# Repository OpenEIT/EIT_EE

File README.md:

# Spectra PDF

The schematic for the 32 electrode EIT system is called Spectra.pdf and is contained in the top level directory. Please let me know if you think it should have any modifications. 

# Eagle_EIT

Note: the following design is an older design for an 8 electrode system. I have a newer better system which was designed in Altium which I'll put up here as soon as crowd supply campaign finalized. In the meantime I'd love it if you wanted to join the mailing list! 

https://www.crowdsupply.com/mindseye-biomedical/spectra

## EIT PCB design in Eagle CAD

Electrical Impedance Tomography is a new way to image conductivity changes inside any mostly liquid medium - such as the human body. It's attractive as it doesn't use ionizing radiation like the X-rays used in a CATSCAN, and could be relatively cheap to mass produce. 

This project is an example of a working system from PCB to firmware to reconstruction algorithm. Further work could certainly improve the resolution, but for now we have functionality in all sub sections. 

This is everything required for the basic 8 electrode design to work. Photo of the assembled PCB included. 

The design is based on the ADuCM350 which has a dedicated high precision front end with 16 bit resolution 160 kSPS data speed.The front end also performs a DFT at the rate of 13.8ms per calculation. This leads to a high performance minimal noise set up, excellent for both R&D or educational purposes. 

In the not too distant future kits may be available with a smaller version of the PCB mounted in a box, an electrode harness for mounting to the body, and all cables required to run. 

This combination would be an excellent educational tool for those researching this area, as it allows you to try most of the reconstruction algorithms or come up with your own and quantify any improvements in results. 

It's the same technique as is used in CATSCAN's, except the current running through the body instead of dangerous ionizing radiation of X-Rays. 

Improvements are welcome to this design. To increase resolution you could make a rotational version which is time resolution limited, or simply add more electrodes and re-compute the reconstruction that way. Another intended improvement is to move to tetrapolar differential electrodes set up. If you'd like to collaborate just pull the repository or email contact@mindseyebiomedical.com

We'd love to hear how you are using this! 

## New Board Design 

We have a newer better board design which is uploaded and called Spectra.pdf. Check it out. 

## Future Plans 

Are hatching! Join the technical discussion list to discuss further at openeit.github.io 

## License 

The Creative Commons Attribution-NonCommercial-ShareAlike 4.0 International License seems to fit best with this project. Check out the human readable summary here: 

<br />This work is licensed under a <a rel="license" href="http://creativecommons.org/licenses/by-nc-sa/4.0/">Creative Commons Attribution-NonCommercial-ShareAlike 4.0 International License</a>.

If you'd like to make a derivative of this project in a commercial setting, we'd love a payment so that we can afford to spend time both maintaining this project and making more projects like this one. If this hybrid open source model works, it would enable open source projects to receive some funding, making the global commons stronger to benefit everyone.

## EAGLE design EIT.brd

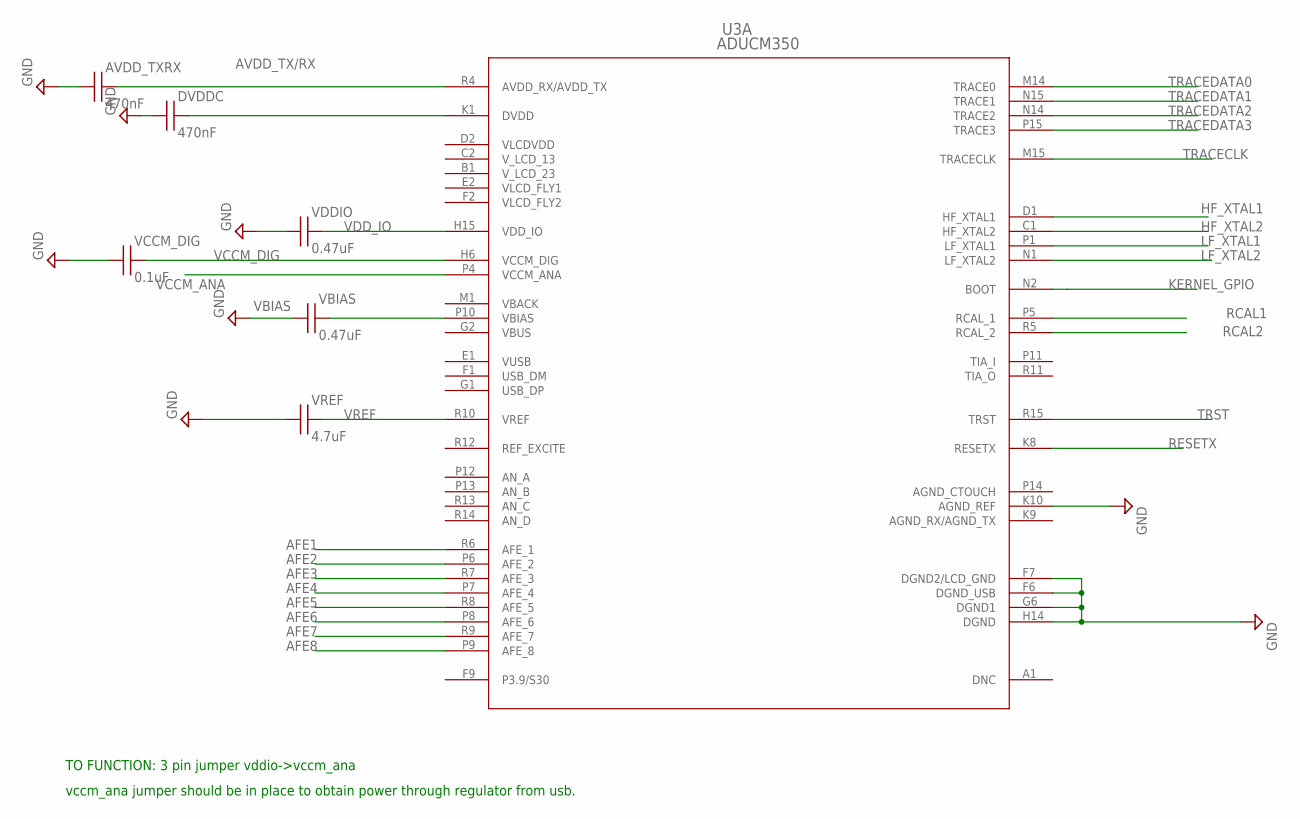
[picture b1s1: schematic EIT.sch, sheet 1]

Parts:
AVDD_TXRX: 470nF; CAPC1608X87N; MPN MCTEA4R7M1HB-0512P
DVDDC: 470nF; CAPC1608X87N; MPN MCTEA4R7M1HB-0512P
U3: ADUCM350; ADUCM350_DUNCAN; MPN ADUCM350BBCZ
VBIAS: 0.47uF; CAPC1608X87N; MPN JMK105BJ474KV-F
VCCM_DIG: 0.1uF; CAPC1608X87N; MPN MC0402X104K100CT
VDDIO: 0.47uF; CAPC1608X87N; MPN JMK105BJ474KV-F
VREF: 4.7uF; CAPC1608X87N; MPN GRM188R60J475ME19D

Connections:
AFE1: U3.R6 (AFE_1); also elsewhere on the board
AFE2: U3.P6 (AFE_2); also elsewhere on the board
AFE3: U3.R7 (AFE_3); also elsewhere on the board
AFE4: U3.P7 (AFE_4); also elsewhere on the board
AFE5: U3.R8 (AFE_5); also elsewhere on the board
AFE6: U3.P8 (AFE_6); also elsewhere on the board
AFE7: U3.R9 (AFE_7); also elsewhere on the board
AFE8: U3.P9 (AFE_8); also elsewhere on the board
AVDD_TX/RX: AVDD_TXRX.2, U3.R4 (AVDD_RX/AVDD_TX)
GND: AVDD_TXRX.1, DVDDC.1, U3.F6 (DGND_USB), U3.F7 (DGND2/LCD_GND), U3.G6 (DGND1), U3.H14 (DGND), U3.K10 (AGND_REF), VBIAS.1, VCCM_DIG.1, VDDIO.1, VREF.1; also elsewhere on the board
HF_XTAL1: U3.D1 (HF_XTAL1); also elsewhere on the board
HF_XTAL2: U3.C1 (HF_XTAL2); also elsewhere on the board
KERNEL_GPIO: U3.N2 (BOOT); also elsewhere on the board
LF_XTAL1: U3.P1 (LF_XTAL1); also elsewhere on the board
LF_XTAL2: U3.N1 (LF_XTAL2); also elsewhere on the board
RCAL1: U3.P5 (RCAL_1); also elsewhere on the board
RCAL2: U3.R5 (RCAL_2); also elsewhere on the board
RESETX: U3.K8 (RESETX); also elsewhere on the board
TRACECLK: U3.M15 (TRACECLK); also elsewhere on the board
TRACEDATA0: U3.M14 (TRACE0); also elsewhere on the board
TRACEDATA1: U3.N15 (TRACE1); also elsewhere on the board
TRACEDATA2: U3.N14 (TRACE2); also elsewhere on the board
TRACEDATA3: U3.P15 (TRACE3); also elsewhere on the board
TRST: U3.R15 (TRST); also elsewhere on the board
VBIAS: U3.P10 (VBIAS), VBIAS.2
VCCM_ANA: U3.P4 (VCCM_ANA); also elsewhere on the board
VCCM_DIG: U3.H6 (VCCM_DIG), VCCM_DIG.2
VDD_IO: U3.H15 (VDD_IO), VDDIO.2; also elsewhere on the board
VLCDVDD: DVDDC.2, U3.K1 (DVDD)
VREF: U3.R10 (VREF), VREF.2

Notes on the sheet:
TO FUNCTION: 3 pin jumper vddio->vccm_ana
vccm_ana jumper should be in place to obtain power through regulator from usb.

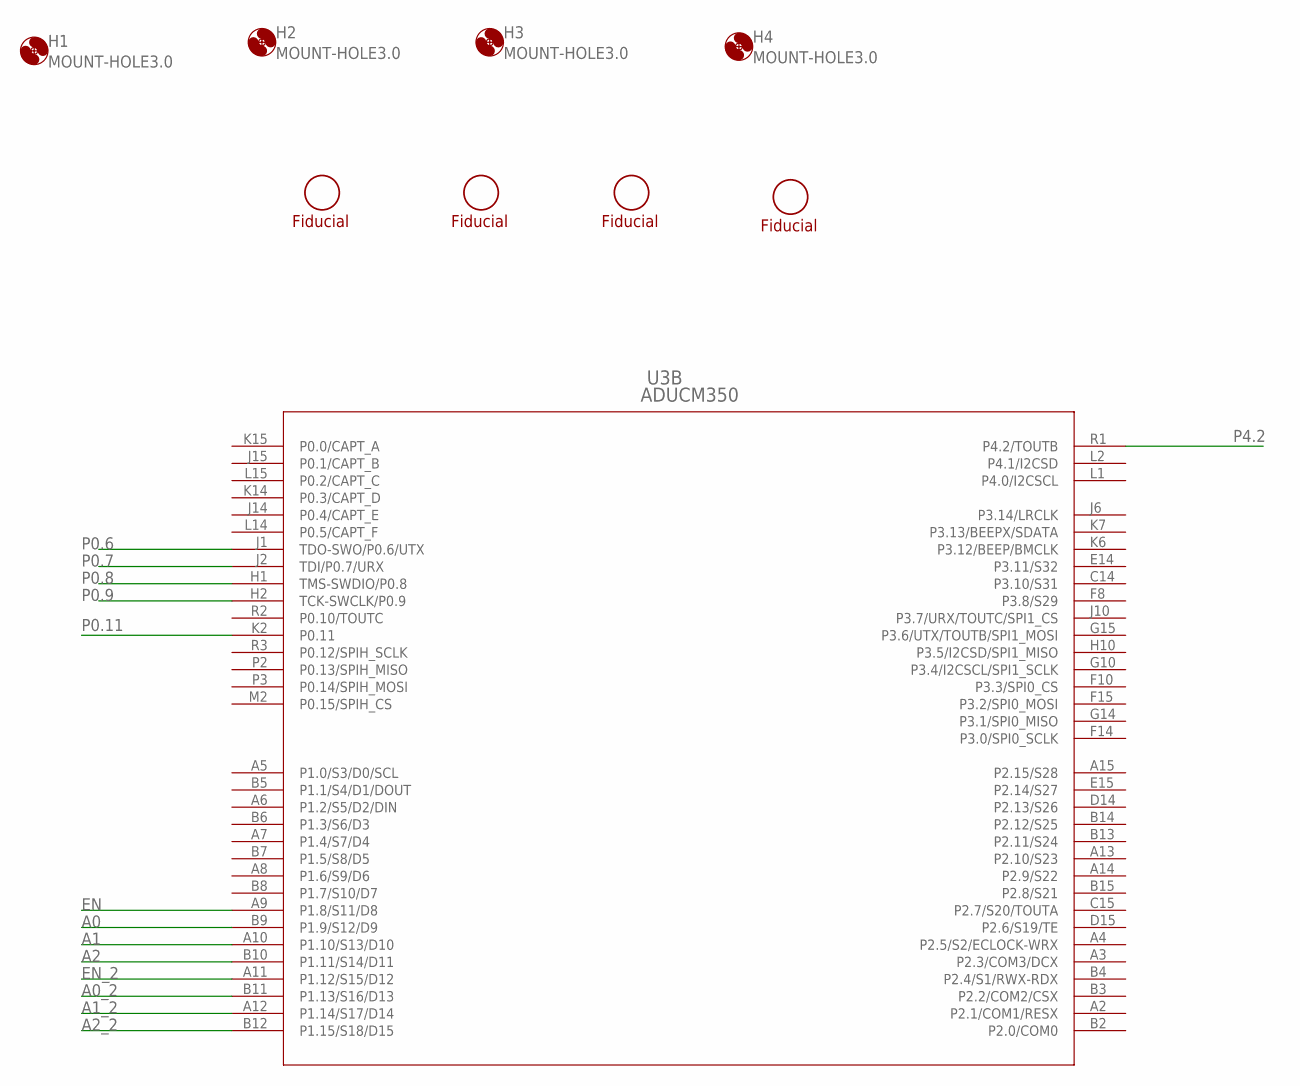
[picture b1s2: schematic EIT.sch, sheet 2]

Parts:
F1, F2, F3, F4: FIDUCIAL; FIDUCIAL-1MM
H1, H2, H3, H4: MOUNT-HOLE3.0; 3,0
U3: ADUCM350; ADUCM350_DUNCAN; MPN ADUCM350BBCZ

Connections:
A0: U3.B9 (P1.9/S12/D9); also elsewhere on the board
A0_2: U3.B11 (P1.13/S16/D13); also elsewhere on the board
A1: U3.A10 (P1.10/S13/D10); also elsewhere on the board
A1_2: U3.A12 (P1.14/S17/D14); also elsewhere on the board
A2: U3.B10 (P1.11/S14/D11); also elsewhere on the board
A2_2: U3.B12 (P1.15/S18/D15); also elsewhere on the board
EN: U3.A9 (P1.8/S11/D8); also elsewhere on the board
EN_2: U3.A11 (P1.12/S15/D12); also elsewhere on the board
P0.6: U3.J1 (TDO-SWO/P0.6/UTX); also elsewhere on the board
P0.7: U3.J2 (TDI/P0.7/URX); also elsewhere on the board
P0.8: U3.H1 (TMS-SWDIO/P0.8); also elsewhere on the board
P0.9: U3.H2 (TCK-SWCLK/P0.9); also elsewhere on the board
P0.11: U3.K2 (P0.11); also elsewhere on the board
P4.2: U3.R1 (P4.2/TOUTB); also elsewhere on the board

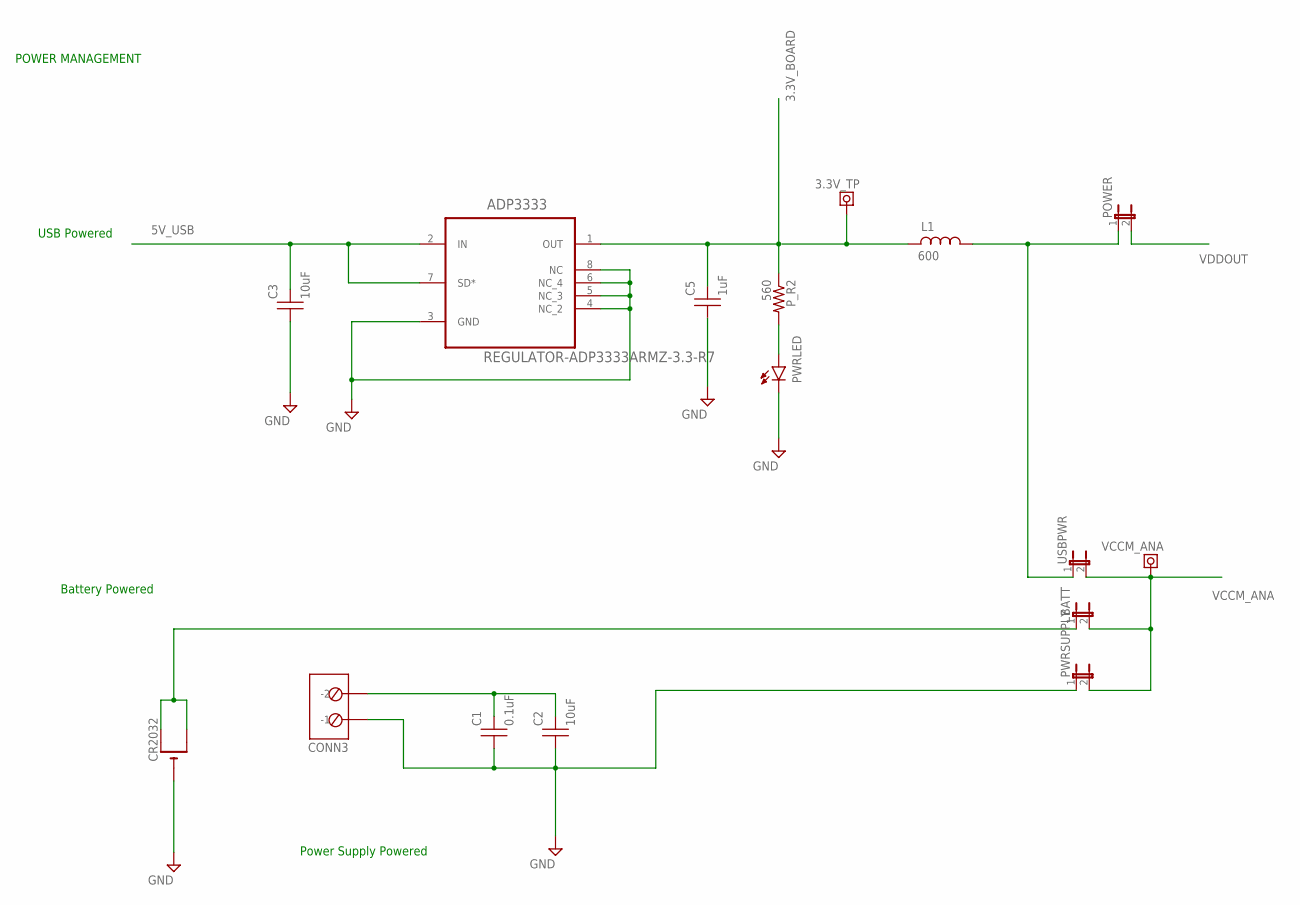
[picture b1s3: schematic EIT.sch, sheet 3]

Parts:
3.3V_TP: TEST_POINT-TEST_POINTMINI; TP-MINI; MPN H2173-05
ADP3333: REGULATOR-ADP3333ARMZ-3.3-R7; SOP65P490X110-8N
BATT: JUMPER-2PTH; 1X02; MPN M20-9990246
C1: 0.1uF; CAPC1608X87N; PARTNO GRM188R71C104KA01D
C2, C3: 10uF; CAPC1608X87N; PARTNO GRM188R60G106ME47D
C5: 1uF; CAPC1608X87N; PARTNO GRM188R60J105KA01D
CONN3: MKDSN2; PARTNO 1729128
CR2032: CR2032SMT; CR2032-SMD; PARTNO 3002TR
L1: 600; CAPC1608X87N; PARTNO BLM18HG601SN1D
POWER: JUMPER-2PTH; 1X02; MPN M20-9990246
PWRLED: LED-0603; 0603_LED; MPN HSML-C191
PWRSUPPLY: JUMPER-2PTH; 1X02; MPN M20-9990246
P_R2: 560; RES1608X55; MPN CRCW0603560RFKEA
USBPWR: JUMPER-2PTH; 1X02; MPN M20-9990246
VCCM_ANA: TEST_POINT-TEST_POINTMINI; TP-MINI; MPN H2173-05

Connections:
3.3V_BOARD: ADP3333.1 (OUT), C5.2, P_R2.2; also elsewhere on the board
5V_USB: ADP3333.2 (IN), ADP3333.7 (SD*), C3.2; also elsewhere on the board
GND: ADP3333.3 (GND), ADP3333.4 (NC_2), ADP3333.5 (NC_3), ADP3333.6 (NC_4), ADP3333.8 (NC), C1.1, C2.1, C3.1, C5.1, CONN3.1 (-1), CR2032.-, PWRLED.C, PWRSUPPLY.1; also elsewhere on the board
unnamed: PWRLED.A, P_R2.1
unnamed: 3.3V_TP.1, L1.1
unnamed: L1.2, POWER.1, USBPWR.1
unnamed: BATT.1, CR2032.+$1 (+), CR2032.+$2 (+1)
unnamed: C1.2, C2.2, CONN3.2 (-2)
VCCM_ANA: BATT.2, PWRSUPPLY.2, USBPWR.2, VCCM_ANA.1; also elsewhere on the board
VDDOUT: POWER.2; also elsewhere on the board

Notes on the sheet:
POWER MANAGEMENT
USB Powered
Battery Powered
Power Supply Powered

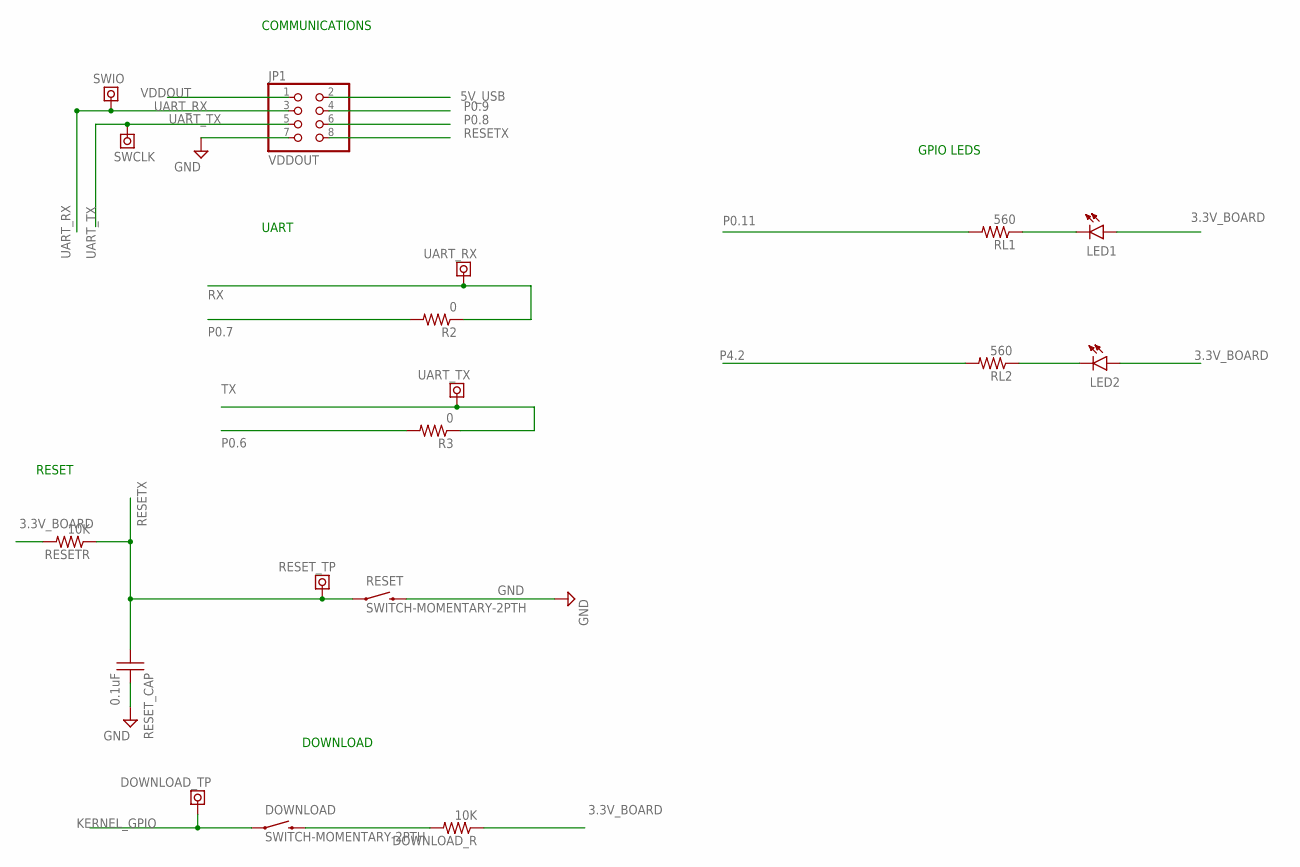
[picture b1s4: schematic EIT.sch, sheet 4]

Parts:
DOWNLOAD: SWITCH-MOMENTARY-2PTH; TACTILE-PTH; MPN B3S-1000
DOWNLOAD_R: 10K; RES1608X55; MPN MC00625W0402110K
DOWNLOAD_TP: TEST_POINT-TEST_POINTMINI; TP-MINI; MPN H2173-05
JP1: VDDOUT; 2X04/90; MPN 27-12209
LED1: LED-0603; 0603_LED; PARTNO 150060YS75000
LED2: LED-0603; 0603_LED; PARTNO 150060GS75000
R2, R3: 0; RES1608X55; PARTNO MCR03EZPJ000
RESET: SWITCH-MOMENTARY-2PTH; TACTILE-PTH; MPN B3S-1000
RESETR: 10K; RES1608X55; PARTNO MCR03EZPFX1002
RESET_CAP: 0.1uF; CAPC1608X87N; MPN C0805C104J5RACTU
RESET_TP: TEST_POINT-TEST_POINTMINI; TP-MINI; MPN H2173-05
RL1, RL2: 560; RES1608X55; PARTNO MCR03ERTF5600
SWCLK: TEST_POINT-TEST_POINTMINI; TP-MINI; MPN H2173-05
SWIO: TEST_POINT-TEST_POINTMINI; TP-MINI; MPN H2173-05
UART_RX: TEST_POINT-TEST_POINTMINI; TP-MINI; MPN H2173-05
UART_TX: TEST_POINT-TEST_POINTMINI; TP-MINI; MPN H2173-05

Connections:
3.3V_BOARD: DOWNLOAD_R.2, LED1.A, LED2.A, RESETR.1; also elsewhere on the board
5V_USB: JP1.2; also elsewhere on the board
GND: JP1.7, RESET.3 (2), RESET_CAP.2; also elsewhere on the board
KERNEL_GPIO: DOWNLOAD.1, DOWNLOAD_TP.1; also elsewhere on the board
unnamed: DOWNLOAD.3 (2), DOWNLOAD_R.1
unnamed: LED2.C, RL2.2
unnamed: LED1.C, RL1.2
P0.6: R3.1; also elsewhere on the board
P0.7: R2.1; also elsewhere on the board
P0.8: JP1.6; also elsewhere on the board
P0.9: JP1.4; also elsewhere on the board
P0.11: RL1.1; also elsewhere on the board
P4.2: RL2.1; also elsewhere on the board
RESETX: JP1.8, RESET.1, RESETR.2, RESET_CAP.1, RESET_TP.1; also elsewhere on the board
RX: R2.2, UART_RX.1; also elsewhere on the board
TX: R3.2, UART_TX.1; also elsewhere on the board
UART_RX: JP1.3, SWIO.1; also elsewhere on the board
UART_TX: JP1.5, SWCLK.1; also elsewhere on the board
VDDOUT: JP1.1; also elsewhere on the board

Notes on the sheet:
COMMUNICATIONS
UART
DOWNLOAD
RESET
GPIO LEDS

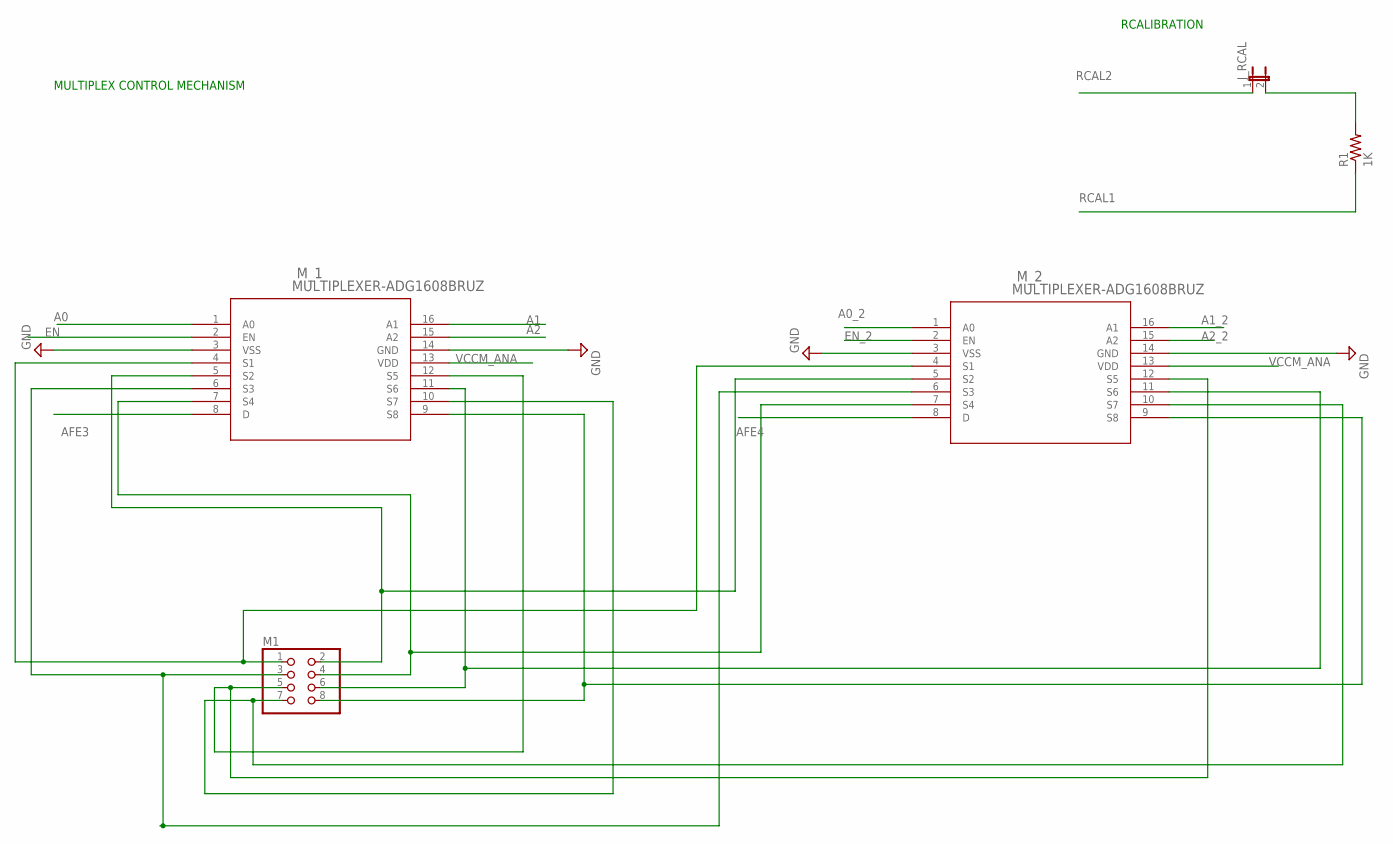
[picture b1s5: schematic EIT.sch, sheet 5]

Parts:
J_RCAL: JUMPER-2PTH; 1X02; MPN M20-9990246
M1: PINHD-2X42X04SHROUDED; 2X04SHROUDED; PARTNO 3020-08-0200-02
M_1, M_2: MULTIPLEXER-ADG1608BRUZ; RU_16; PARTNO ADG1608BRUZ
R1: 1K; 0603-RES; MPN ERJ-3EKF1001V

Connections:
A0: M_1.1 (A0); also elsewhere on the board
A0_2: M_2.1 (A0); also elsewhere on the board
A1: M_1.16 (A1); also elsewhere on the board
A1_2: M_2.16 (A1); also elsewhere on the board
A2: M_1.15 (A2); also elsewhere on the board
A2_2: M_2.15 (A2); also elsewhere on the board
AFE3: M_1.8 (D); also elsewhere on the board
AFE4: M_2.8 (D); also elsewhere on the board
EN: M_1.2 (EN); also elsewhere on the board
EN_2: M_2.2 (EN); also elsewhere on the board
GND: M_1.3 (VSS), M_1.14 (GND), M_2.3 (VSS), M_2.14 (GND); also elsewhere on the board
M2_1: M1.1, M_1.4 (S1), M_2.4 (S1)
M2_2: M1.2, M_1.5 (S2), M_2.5 (S2)
M2_3: M1.3, M_1.6 (S3), M_2.6 (S3)
M2_4: M1.4, M_1.7 (S4), M_2.7 (S4)
M2_7: M1.7, M_1.10 (S7), M_2.10 (S7)
M2_8: M1.8, M_1.9 (S8), M_2.9 (S8)
unnamed: M1.5, M_1.12 (S5), M_2.12 (S5)
unnamed: J_RCAL.2, R1.2
unnamed: M1.6, M_1.11 (S6), M_2.11 (S6)
RCAL1: R1.1; also elsewhere on the board
RCAL2: J_RCAL.1; also elsewhere on the board
VCCM_ANA: M_1.13 (VDD), M_2.13 (VDD); also elsewhere on the board

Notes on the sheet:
MULTIPLEX CONTROL MECHANISM
RCALIBRATION

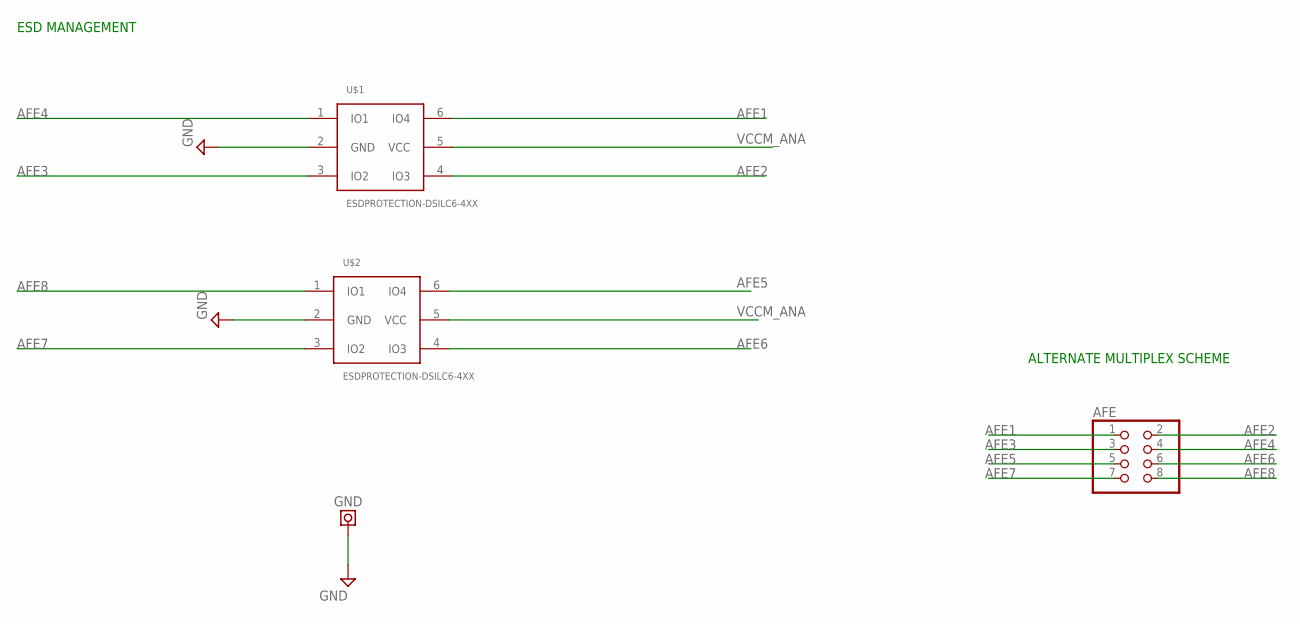
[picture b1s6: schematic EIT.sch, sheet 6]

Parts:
AFE: PINHD-2X42X04SHROUDED; 2X04SHROUDED; PARTNO 3020-08-0200-02
GND: TEST_POINT-TEST_POINTMINI; TP-MINI; PARTNO 5003
U$1, U$2: ESDPROTECTION-DSILC6-4XX; SOT-666; MPN DSILC6-4P6

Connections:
AFE1: AFE.1, U$1.6 (IO4); also elsewhere on the board
AFE2: AFE.2, U$1.4 (IO3); also elsewhere on the board
AFE3: AFE.3, U$1.3 (IO2); also elsewhere on the board
AFE4: AFE.4, U$1.1 (IO1); also elsewhere on the board
AFE5: AFE.5, U$2.6 (IO4); also elsewhere on the board
AFE6: AFE.6, U$2.4 (IO3); also elsewhere on the board
AFE7: AFE.7, U$2.3 (IO2); also elsewhere on the board
AFE8: AFE.8, U$2.1 (IO1); also elsewhere on the board
GND: GND.1, U$1.2 (GND), U$2.2 (GND); also elsewhere on the board
VCCM_ANA: U$1.5 (VCC), U$2.5 (VCC); also elsewhere on the board

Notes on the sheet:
ESD MANAGEMENT
ALTERNATE MULTIPLEX SCHEME

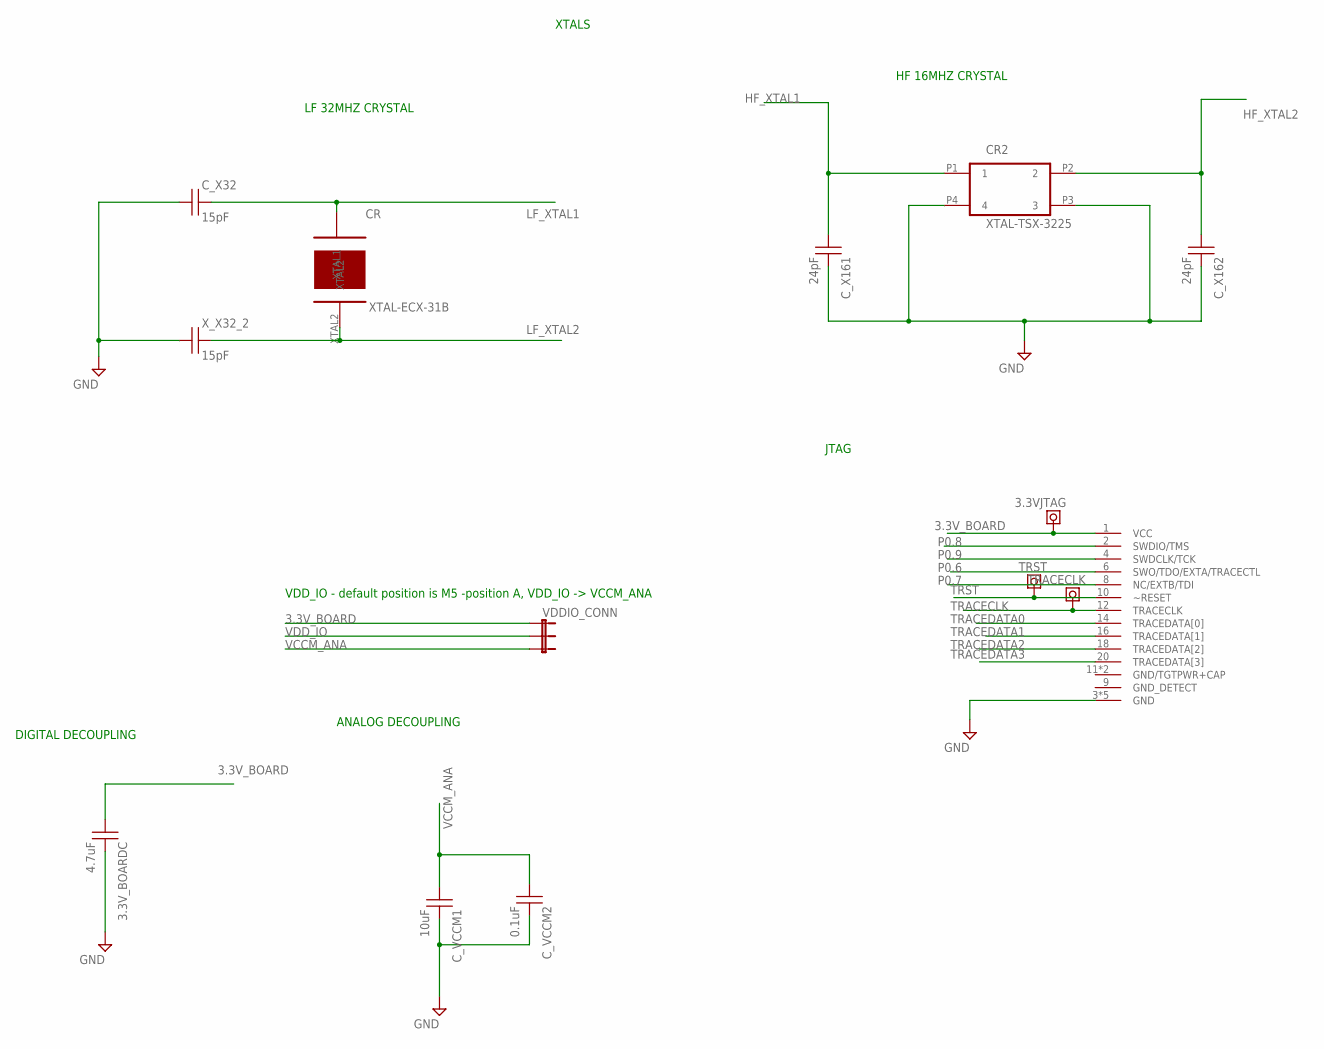
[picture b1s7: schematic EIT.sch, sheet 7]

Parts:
3.3VJTAG: TEST_POINT-TEST_POINTMINI; TP-MINI; PARTNO 5003
3.3V_BOARDC: 4.7uF; CAPC1608X87N; MPN GRM188R60J475ME19D
CR: XTAL-ECX-31B; PARTNO ECS-.327-7-34B-TR
CR2: XTAL-TSX-3225; TSX-3225; PARTNO FA-238 16.0000MB-K3
C_VCCM1: 10uF; CAPC1608X87N; MPN C0805C106Z8VACTU
C_VCCM2: 0.1uF; CAPC1608X87N; MPN MC0402X104K100CT
C_X32: 15pF; CAPC1608X87N; MPN GRM188R60J475ME19D
C_X161, C_X162: 24pF; CAPC1608X87N; MPN MC0402X104K100CT
TRACECLK: TEST_POINT-TEST_POINTMINI; TP-MINI; PARTNO 5003
TRST: TEST_POINT-TEST_POINTMINI; TP-MINI; PARTNO 5003
U$11: 2X10_0.05"_CORTEX_DEBUG_WITH_ETMSMD_SHROUDED; 2X10_0.05"_SMD_SH; PARTNO EHF-110-01-L-D-SM
VDDIO_CONN: JUMPER-3PTH; 1X03; MPN M20-9990345
X_X32_2: 15pF; CAPC1608X87N; MPN GRM188R60J475ME19D

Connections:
3.3V_BOARD: 3.3VJTAG.1, 3.3V_BOARDC.1, U$11.1 (VCC), VDDIO_CONN.1; also elsewhere on the board
GND: 3.3V_BOARDC.2, CR2.P3 (3), CR2.P4 (4), C_VCCM1.2, C_VCCM2.2, C_X32.1, C_X161.2, C_X162.2, U$11.3 (GND), U$11.5 (GND), U$11.15 (GND), U$11.17 (GND), U$11.19 (GND), X_X32_2.1; also elsewhere on the board
HF_XTAL1: CR2.P1 (1), C_X161.1; also elsewhere on the board
HF_XTAL2: CR2.P2 (2), C_X162.1; also elsewhere on the board
LF_XTAL1: CR.XTAL1, C_X32.2; also elsewhere on the board
LF_XTAL2: CR.XTAL2, X_X32_2.2; also elsewhere on the board
P0.6: U$11.6 (SWO/TDO/EXTA/TRACECTL); also elsewhere on the board
P0.7: U$11.8 (NC/EXTB/TDI); also elsewhere on the board
P0.8: U$11.2 (SWDIO/TMS); also elsewhere on the board
P0.9: U$11.4 (SWDCLK/TCK); also elsewhere on the board
TRACECLK: TRACECLK.1, U$11.12 (TRACECLK); also elsewhere on the board
TRACEDATA0: U$11.14 (TRACEDATA[0]); also elsewhere on the board
TRACEDATA1: U$11.16 (TRACEDATA[1]); also elsewhere on the board
TRACEDATA2: U$11.18 (TRACEDATA[2]); also elsewhere on the board
TRACEDATA3: U$11.20 (TRACEDATA[3]); also elsewhere on the board
TRST: TRST.1, U$11.10 (~RESET); also elsewhere on the board
VCCM_ANA: C_VCCM1.1, C_VCCM2.1, VDDIO_CONN.3; also elsewhere on the board
VDD_IO: VDDIO_CONN.2; also elsewhere on the board

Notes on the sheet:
VDD_IO - default position is M5 -position A, VDD_IO -> VCCM_ANA
DIGITAL DECOUPLING
ANALOG DECOUPLING
JTAG
XTALS
LF 32MHZ CRYSTAL
HF 16MHZ CRYSTAL

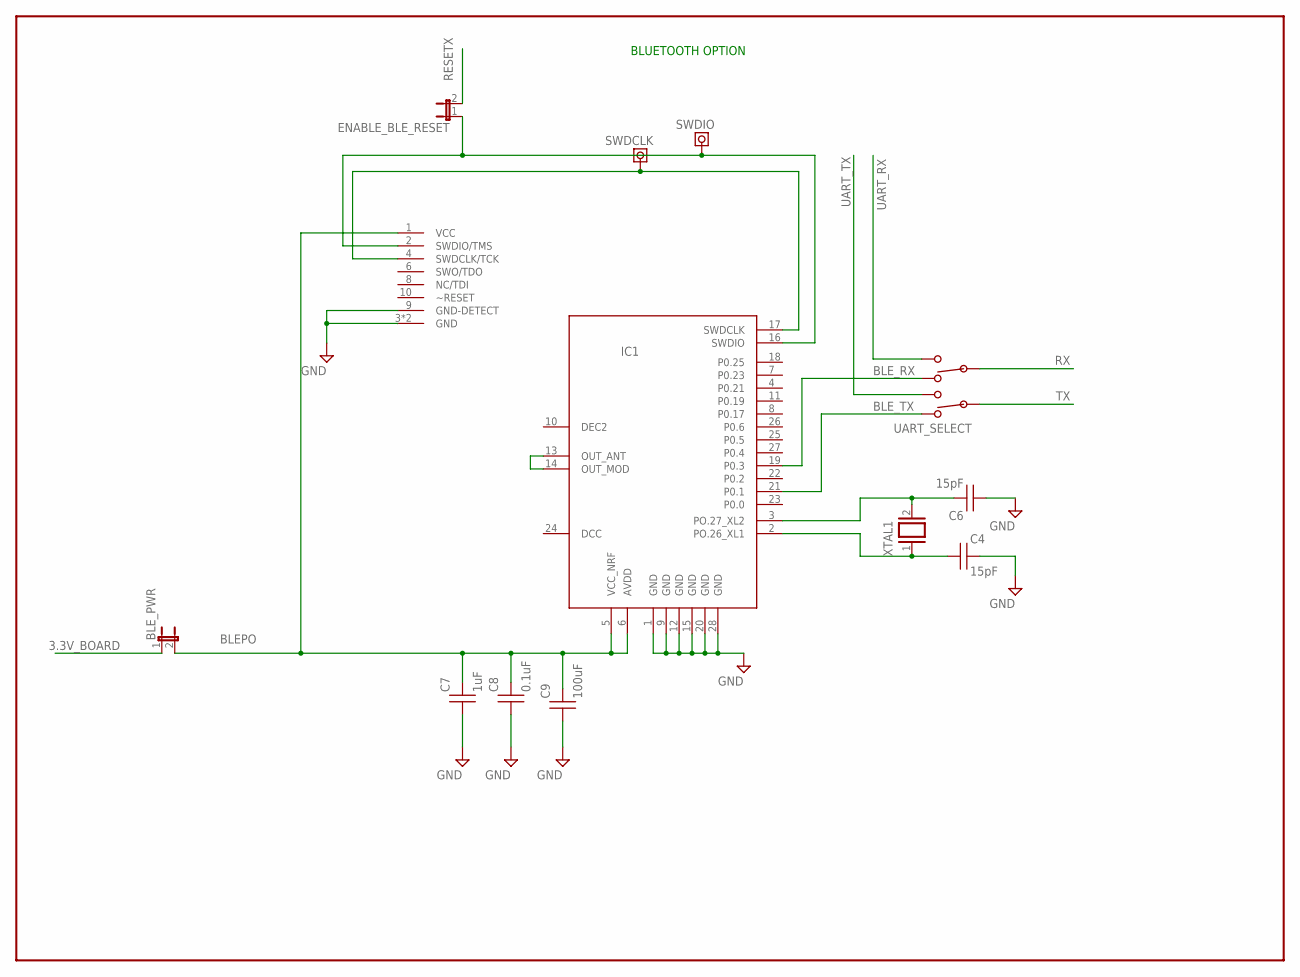
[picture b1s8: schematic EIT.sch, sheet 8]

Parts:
BLE_PWR: JUMPER-2PTH; 1X02; PARTNO M20-9990246
C4, C6: 15pF; CAPC1608X87N; PARTNO GRM1885C1H150JA01D
C7: 1uF; CAPC1608X87N; PARTNO GRM188R60J105KA01D
C8: 0.1uF; CAPC1608X87N; PARTNO GRM188R71C104KA01D
C9: 100uF; CAP2012X100N; PARTNO GRM21BR60G107ME15L
ENABLE_BLE_RESET: JUMPER-2PTH; 1X02; PARTNO M20-9990246
IC1: TY-EYSGJNAWY-1X; TY-EYSGJN; PARTNO EYSGJNAWY-1X
SWDCLK: TEST_POINT-TEST_POINTMINI; TP-MINI; PARTNO 5003
SWDIO: TEST_POINT-TEST_POINTMINI; TP-MINI; PARTNO 5003
U$10: 2X5_0.05"_CORTEX_DEBUGSMD_SHROUDED; 2X5_0.05"_SMD_SH; PARTNO SHF-105-01-L-D-SM-LC
UART_SELECT: SWITCH-DPDT; SWITCH-G13AH; PARTNO G22AP
XTAL1: XTAL_BLE-2-SMD; FC-12M; PARTNO SER3673CT-ND

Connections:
3.3V_BOARD: BLE_PWR.1; also elsewhere on the board
BLEPO: BLE_PWR.2, C7.2, C8.2, C9.2, IC1.5 (VCC_NRF), IC1.6 (AVDD), U$10.1 (VCC)
BLE_RX: IC1.19 (P0.3), UART_SELECT.1
BLE_TX: IC1.21 (P0.1), UART_SELECT.4
GND: C4.2, C6.1, C7.1, C8.1, C9.1, IC1.1 (GND), IC1.9 (GND), IC1.12 (GND), IC1.15 (GND), IC1.20 (GND), IC1.28 (GND), U$10.3 (GND), U$10.5 (GND), U$10.9 (GND-DETECT); also elsewhere on the board
unnamed: IC1.13 (OUT_ANT), IC1.14 (OUT_MOD)
unnamed: C4.1, IC1.2 (PO.26_XL1), XTAL1.1
unnamed: C6.2, IC1.3 (PO.27_XL2), XTAL1.2
unnamed: IC1.17 (SWDCLK), SWDCLK.1, U$10.4 (SWDCLK/TCK)
unnamed: ENABLE_BLE_RESET.1, IC1.16 (SWDIO), SWDIO.1, U$10.2 (SWDIO/TMS)
RESETX: ENABLE_BLE_RESET.2; also elsewhere on the board
RX: UART_SELECT.2; also elsewhere on the board
TX: UART_SELECT.5; also elsewhere on the board
UART_RX: UART_SELECT.3; also elsewhere on the board
UART_TX: UART_SELECT.6; also elsewhere on the board

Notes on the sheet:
BLUETOOTH OPTION

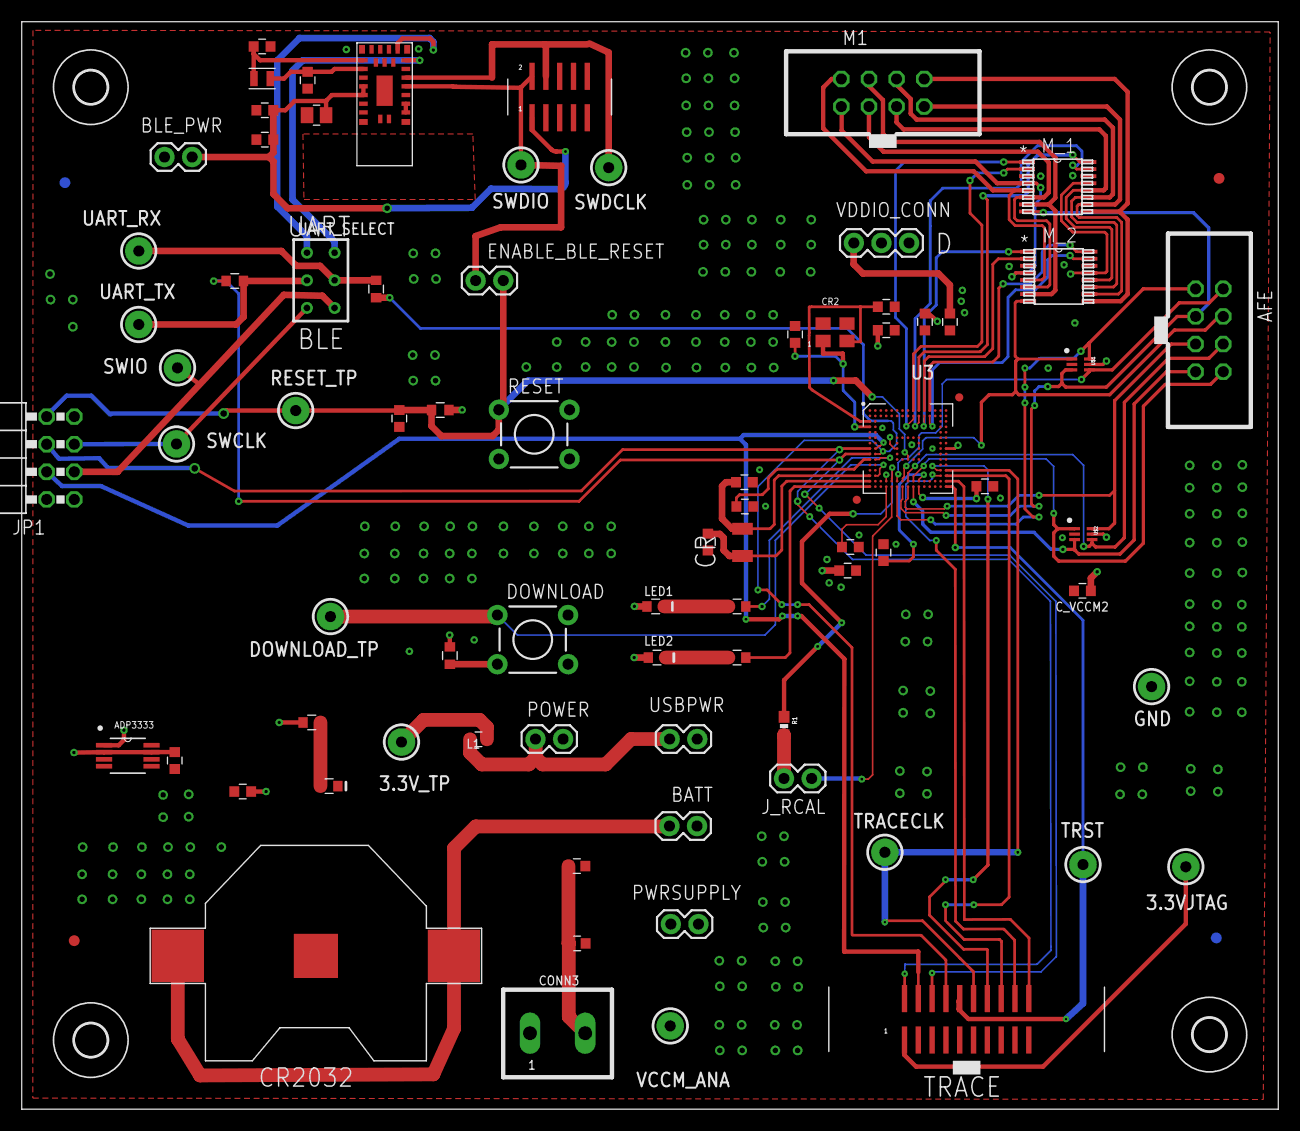
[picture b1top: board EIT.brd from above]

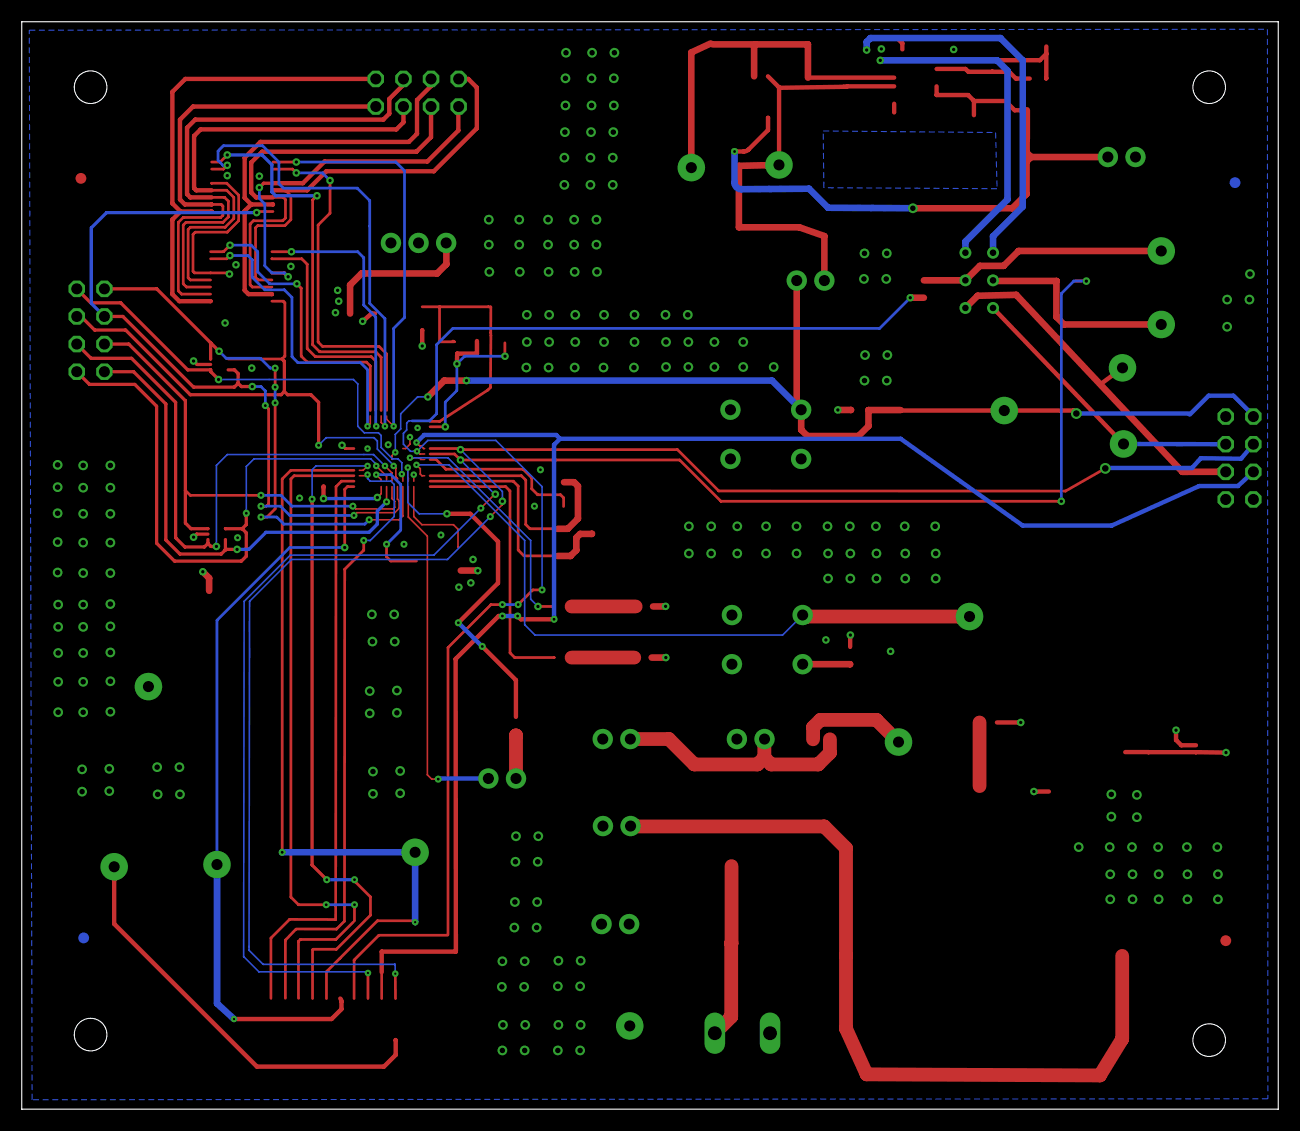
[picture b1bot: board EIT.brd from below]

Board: 4 copper layers, 115.5 x 100.0 mm, 85 parts (2 on the bottom side), 76 nets.

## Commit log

2017-11-22 8 electrode EIT system
2017-11-22 Create LICENSE
2017-11-27 readme improvements
2017-11-27 readme improvement
2018-01-17 EIT schematic added
2018-07-29 CC BY-NC-SA 4.0
    See https://creativecommons.org/licenses/by-nc-sa/4.0/ for details.
2018-10-19 This is my first test.
2019-01-18 readme changes
2019-01-18 readme update
2019-04-08 8 electrode flex gerbers added
2021-01-27 Update README.md
    updated readme to included note on spectra schematic.

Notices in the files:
parts and their libraries:
SparkFun-Resistors: Licensing: Creative Commons ShareAlike 4.0 International - https://creativecommons.org/licenses/by-sa/4.0
